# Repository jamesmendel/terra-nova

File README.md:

<h1 align="center">TERRA is a companion for mindful wandering</h1>
<h2 align="center">⭐️ This is the working repository for the second generation of TERRA hardware and software. ⭐️</h2>

<br> <!-- Additional spacing -->
<br> <!-- Additional spacing -->

<br> <!-- Additional spacing -->
<br> <!-- Additional spacing -->

##  Designed with the science of AI and the wisdom of mindfulness, TERRA is the incredible, pocket-sized compass that lets you wander without getting lost. Leave your phone behind and reconnect with your surroundings.

<br> <!-- Additional spacing -->

### Features
- **Improvised Trails, Powered by AI**: Every journey begins with a prompt. TERRA’s sophisticated AI translates your intentions, available time, and precise location into a tailored trail of GPS coordinates. Users don't know where TERRA will take them; the only certainty is finding their way back to the starting point.
- **Wander Without Your Phone**: TERRA invites users to leave their smartphones behind and reconnect with their surroundings. The standalone device boasts a minimalist interface, featuring a tranquil compass needle and gentle haptic feedback to ensure users remain engaged with the present moment.  
- **Open-Source by Design**: TERRA is designed with a DIY mindset. Anyone can download the open-source software, 3D print the CAD designs, assemble the necessary hardware, and start wandering.

<br> <!-- Additional spacing -->

<p align="center">
  ⚠️ <strong>NOTICE</strong>: This project is currently in an experimental phase and is undergoing rapid developments ⚠️
</p>

<br> <!-- Additional spacing -->

### Software

The TERRA App generates coordinates or checkpoints from a starting point and an ideal trail length using the ChatGPT API.

### Running TERRA App Locally

#### Prerequisites 
- `Node.js` v21.5
- `body-parser` v1.20.2
- `cors` v2.8.5
- `express` v4.19.0
- `node-fetch` v3.3.2

To run the TERRA App locally, follow these steps:

1. **Implement ChatGPT API Key:** Obtain a [ChatGPT API key](https://platform.openai.com/) and replace ```YOUR_OPENAI_API_KEY``` with it in the ```server.js``` file.
2. **Implement Google Maps API Key:** Obtain a [Google Places API key](https://developers.google.com/maps/documentation/places/web-service/overview) and replace ```YOUR_MAPS_KEY``` with it in the ```index.js``` file.
3. **Run Locally:** To run the application, use the command:
    ```
    node server.js
    ```
4. **Load Application:** Open `index.html` in a browser to use the app for generating a route.
5. **Download config.h File:** Download the `config.h` file which contains the generated route configuration.
6. **Update Arduino Code:** Replace the `config.h` file in the Arduino code directory with the newly downloaded file.

### Hardware

The hardware for the TERRA project is based on an ESP32 device, equipped with a range of sensors for navigation and interaction.

### Components

The main components required are:

- ESP32 Feather V2 [link](https://learn.adafruit.com/adafruit-esp32-feather-v2/pinouts)
- Waveshare 1.28" Round LCD Display Module with GC9A01 Driver [link](https://www.waveshare.com/1.28inch-lcd-module.htm)
- Adafruit Push-button Power Switch [link](https://thepihut.com/products/adafruit-push-button-power-switch-breakout)
- Beitian BN 880 GPS module [link](https://store.beitian.com/products/beitian-compass-qmc5883l-amp2-6-pix4-pixhawk-gnss-gps-glonass-dual-flight-control-gps-module-bn-880q?variant=44696120295711)
- Adafruit DRV2605L Haptic Controller Breakout [link](https://learn.adafruit.com/adafruit-drv2605-haptic-controller-breakout/arduino-code)
- CMPS12 Compass [link](https://www.robot-electronics.co.uk/cmps12-tilt-compensated-magnetic-compass.html)
- Round Battery
- USB C charging port extender

### Wiring
Connect the components together in the following order:

| ESP32 Pin | Screen | Motor Driver | Compass | GPS | Push Button |
| --------- | ------ | ------------ | ------- | --- | ----------- |
| 3V        | VCC    | VIN          | VIN     | VIN |             |
| GND       | GND    | GND          | GND     | GND | GND         |
| 19 (MOSI) | DIN    |              |         |     |             |
| 4 (A5)    | RST    |              |         |     |             |
| 5 (SCK)   | CLK    |              |         |     |             |
| 12        | BL     |              |         |     |             |
| 15        | CS     |              |         |     |             |
| 32 (A7)   |        |              |         |     | OFF         |
| 33        | DC     |              |         |     |             |
| SDA       |        | SDA          | SDA     |     |             |
| SCL       |        | SCL          | SCL     |     |             |
| RX        |        |              |         | TX  |             |
| TX        |        |              |         | RX  |             |

## Arduino Code

To run the Arduino code, you will need to set up the ESP32 board and install the necessary libraries.

### Setup Steps

1. **ESP32 Arduino Setup:** Add the ESP32 board to the Arduino IDE.
    - Go to **Arduino > Preferences**.
    - Add the following URL to the **Additional Boards Manager URLs**:
      ```
      https://raw.githubusercontent.com/espressif/arduino-esp32/gh-pages/package_esp32_dev_index.json
      ```
    - Select **Adafruit Feather ESP32 V2** as the board.

2. **Install Libraries:** Install the following libraries through the Library Manager in the Arduino IDE.
    - `TinyGPSPlus.h`
    - `TFT_eSPI.h`
    - `Adafruit_DRV2605.h`

3. **Upload the Code:** After installing the libraries and updating the `config.h` file with new coordinates, upload the code to the ESP32 device. The device should work without further adjustments.

4. **Debug Mode:** A `debugMode` flag is available in the code. To test the device with manual coordinates, set this flag to `true` and input coordinates into the serial monitor.

### Further Customizations

You can use your own checkpoint files by converting black and white images into a compatible format.

#### Using Your Own Checkpoint Files

- Convert static black and white, 240x240PX `.bmp` images to `.XBM` format using [this online tool](https://www.online-utility.org/image/convert/to/XBM).
- Open the XBM file in a text editor and copy the hexadecimal values included in the curly brackets.
- Replace the existing files in the `images/checkpoints` directory with your customized `.h` file.

### Contributors
Vision + Concept: Modem<br> 
Industrial Design: Panter&Tourron<br> 
Software + Hardware: Alice Stewart<br> 
Product Renderings: Côme Lart<br> 
Illustrations: Hugo Bernier<br> 
Campaign Teaser: Michael Willis

### License
TERRA is licensed under the GNU General Public License v3.0 © 2024 Modem

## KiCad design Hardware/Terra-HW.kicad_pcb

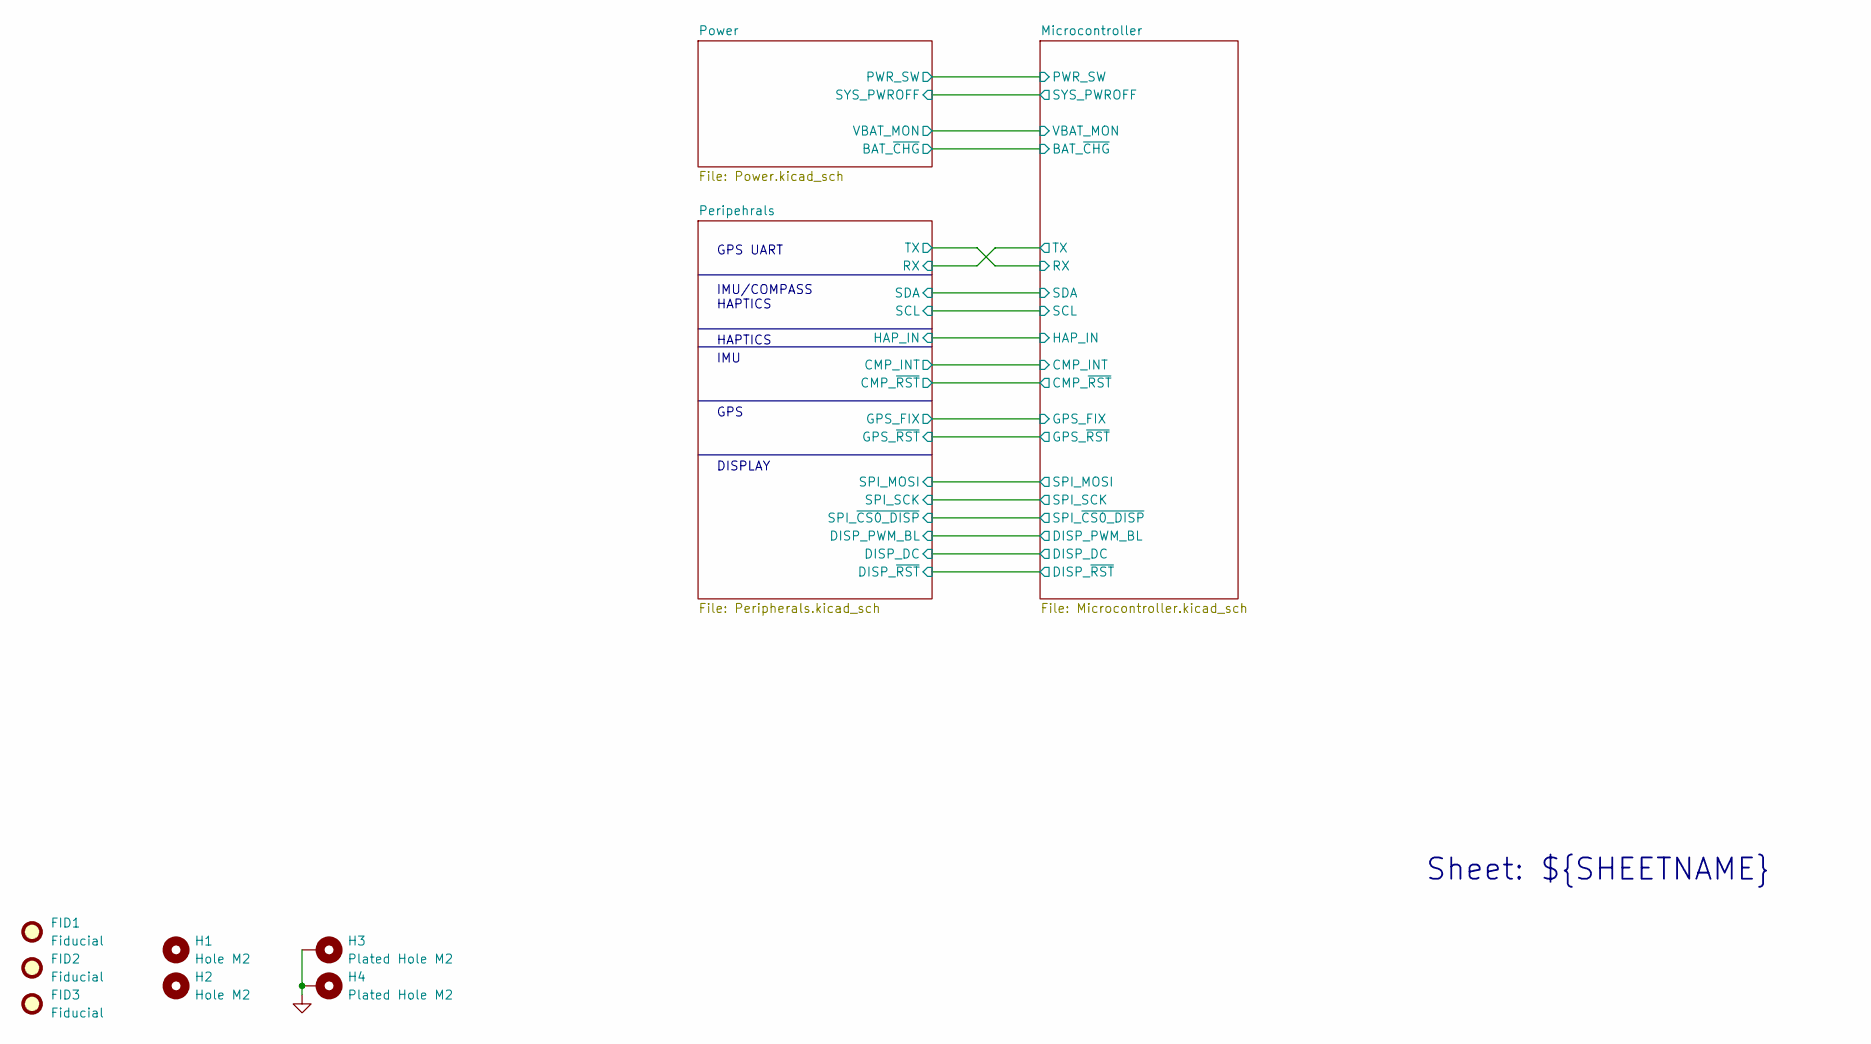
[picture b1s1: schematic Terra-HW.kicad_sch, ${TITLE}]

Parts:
FID1, FID2, FID3: Fiducial; Fiducial_1mm_Mask2mm
H1, H2: Hole M2; MountingHole_2.2mm_M2
H3, H4: Plated Hole M2; MountingHole_2.2mm_M2_Pad

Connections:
GND: H3.1, H4.1; also elsewhere on the board

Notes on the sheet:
HAPTICS
GPS UART
IMU
DISPLAY
IMU/COMPASS HAPTICS
GPS
Sheet: ${SHEETNAME}

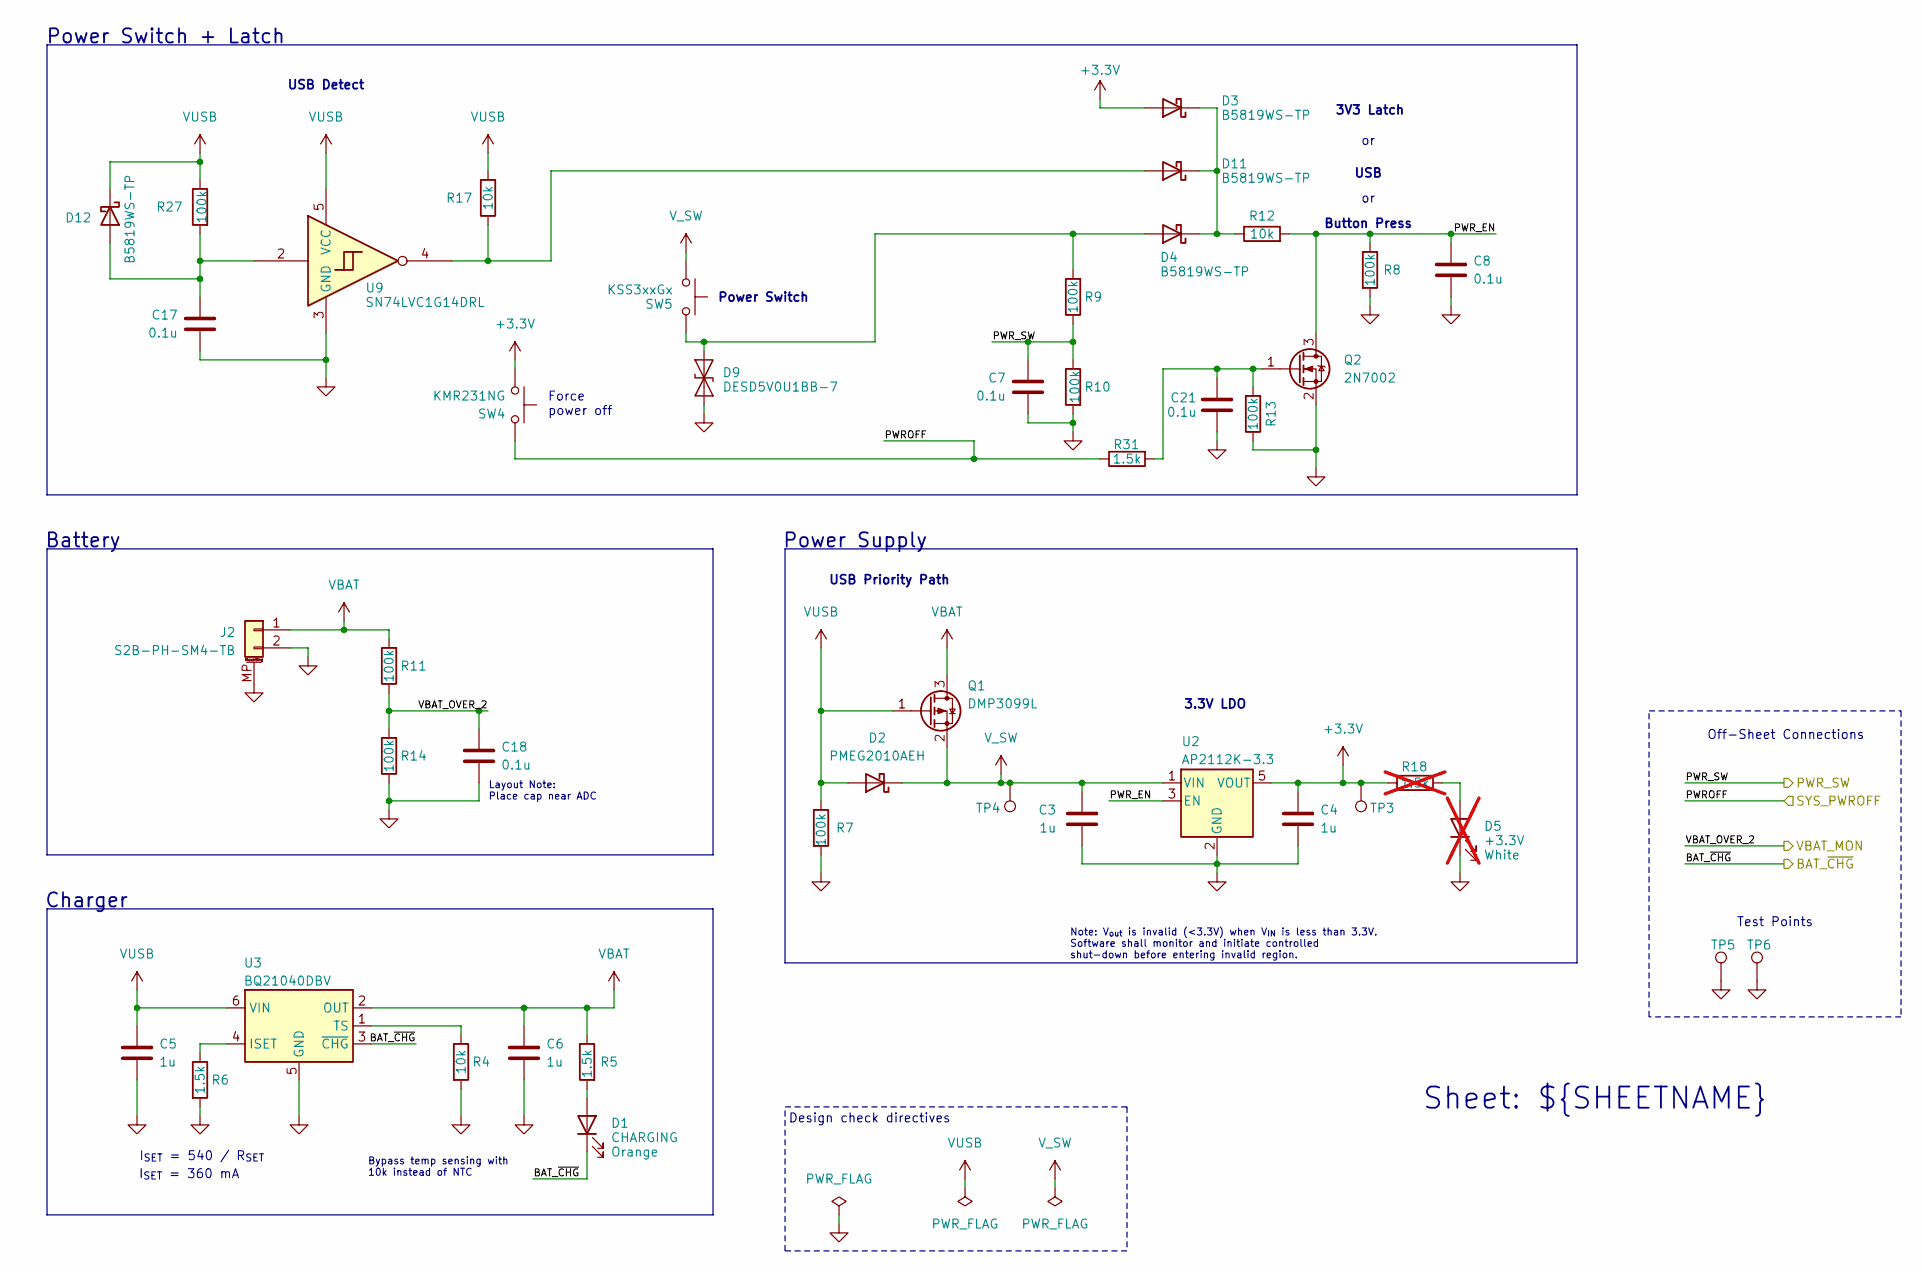
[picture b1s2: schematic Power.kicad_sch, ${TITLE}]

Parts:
C3, C4, C5, C6: 1u; C_0603_1608Metric; MPN CL10A105KO8NNNC
C7, C8, C17, C18, C21: 0.1u; C_0603_1608Metric; MPN CL10B104KO8NNNC
D1: CHARGING; D_0603_1608Metric; MPN LTST-C190KFKT
D2: PMEG2010AEH; D_SOD-123; MPN PMEG2010AEH,115
D3, D4, D11, D12: B5819WS-TP; D_SOD-323; MPN B5819WS-TP
D5: +3.3V; D_0603_1608Metric; MPN IN-S63AT5UW; not fitted
D9: DESD5V0U1BB-7; D_SOD-523; MPN DESD5V0U1BB-7
J2: S2B-PH-SM4-TB; JST_PH_S2B-PH-SM4-TB_1x02-1MP_P2.00mm_Horizontal; MPN S2B-PH-SM4-TB
Q1: DMP3099L; SOT-23; MPN DMP3099L
Q2: 2N7002; SOT-23; MPN 2N7002
R4, R12, R17: 10k; R_0603_1608Metric; MPN RC0603FR-0710KL
R5, R6, R31: 1.5k; R_0603_1608Metric; MPN RC0603FR-071K5L
R7, R8, R9, R10, R11, R13, R14, R27: 100k; R_0603_1608Metric; MPN RC0603FR-07100KL
R18: 1.5k; R_0603_1608Metric; MPN RC0603FR-071K5L; not fitted
SW4: KMR231NG; SW_Push_1P1T_NO_CK_KMR2; MPN KMR231NG
SW5: KSS3xxGx; SW_KSS323_CNK; MPN KSS321GLFS
TP3: 3.3V; TestPoint_Pad_D1.5mm_WITH_LABEL
TP4: V_SW; TestPoint_Pad_D1.5mm_WITH_LABEL
TP5, TP6: GND; TestPoint_Pad_D1.5mm_WITH_LABEL
U2: AP2112K-3.3; SOT-23-5; MPN AP2112K-3.3TRG1
U3: BQ21040DBV; SOT-23-6; MPN BQ21040DBVR
U9: SN74LVC1G14DRL; SOT-553; MPN SN74LVC1G14DRLR

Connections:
+3.3V: C4.1, D3.2 (A), R18.1, SW4.1, TP3.1, U2.5 (VOUT); also elsewhere on the board
/Microcontroller/BAT_~CHG: D1.1 (K), U3.3 (~CHG); also elsewhere on the board
/Microcontroller/PWROFF: R31.1, SW4.2; also elsewhere on the board
/Microcontroller/PWR_SW: C7.1, R9.1, R10.1; also elsewhere on the board
/Microcontroller/VBAT_OVER_2: C18.1, R11.1, R14.2; also elsewhere on the board
/Power/PWR_EN: C8.1, Q2.3 (D), R8.1, R12.2, U2.3 (EN)
GND: C3.2, C4.2, C5.2, C6.2, C7.2, C8.2, C17.2, C18.2, C21.2, D5.1 (K), D9.1 (A1), J2.2, J2.MP (MountPin), Q2.2 (S), R4.2, R6.2, R7.2, R8.2, R10.2, R13.1, R14.1, TP5.1, TP6.1, U2.2 (GND), U3.5 (GND), U9.3 (GND); also elsewhere on the board
unnamed: D1.2 (A), R5.2
unnamed: D4.2 (A), D9.2 (A2), R9.2, SW5.2
unnamed: D5.2 (A), R18.2
unnamed: D11.2 (A), R17.1, U9.4
unnamed: D3.1 (K), D4.1 (K), D11.1 (K), R12.1
unnamed: C17.1, D12.2 (A), R27.2, U9.2
unnamed: C21.1, Q2.1 (G), R13.2, R31.2
unnamed: R6.1, U3.4 (ISET)
unnamed: R4.1, U3.1 (TS)
VBAT: C6.1, J2.1, Q1.3 (D), R5.1, R11.2, U3.2 (OUT); also elsewhere on the board
VUSB: C5.1, D2.2 (A), D12.1 (K), Q1.1 (G), R7.1, R17.2, R27.1, U3.6 (VIN), U9.5 (VCC); also elsewhere on the board
V_SW: C3.1, D2.1 (K), Q1.2 (S), SW5.1, TP4.1, U2.1 (VIN)

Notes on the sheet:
Power Switch
Power Supply
I_{SET} = 540 / R_{SET}
3V3 Latch
3.3V LDO
USB Priority Path
Note: V_{out} is invalid (<3.3V) when V_{IN} is less than 3.3V. Software shall monitor and initiate controlled shut-down before entering invalid region.
Force power off
Test Points
Bypass temp sensing with 10k instead of NTC
Charger
Design check directives
I_{SET} = 360 mA
Button Press
Layout Note: Place cap near ADC
USB Detect
Battery
Off-Sheet Connections
USB
Power Switch + Latch
Sheet: ${SHEETNAME}

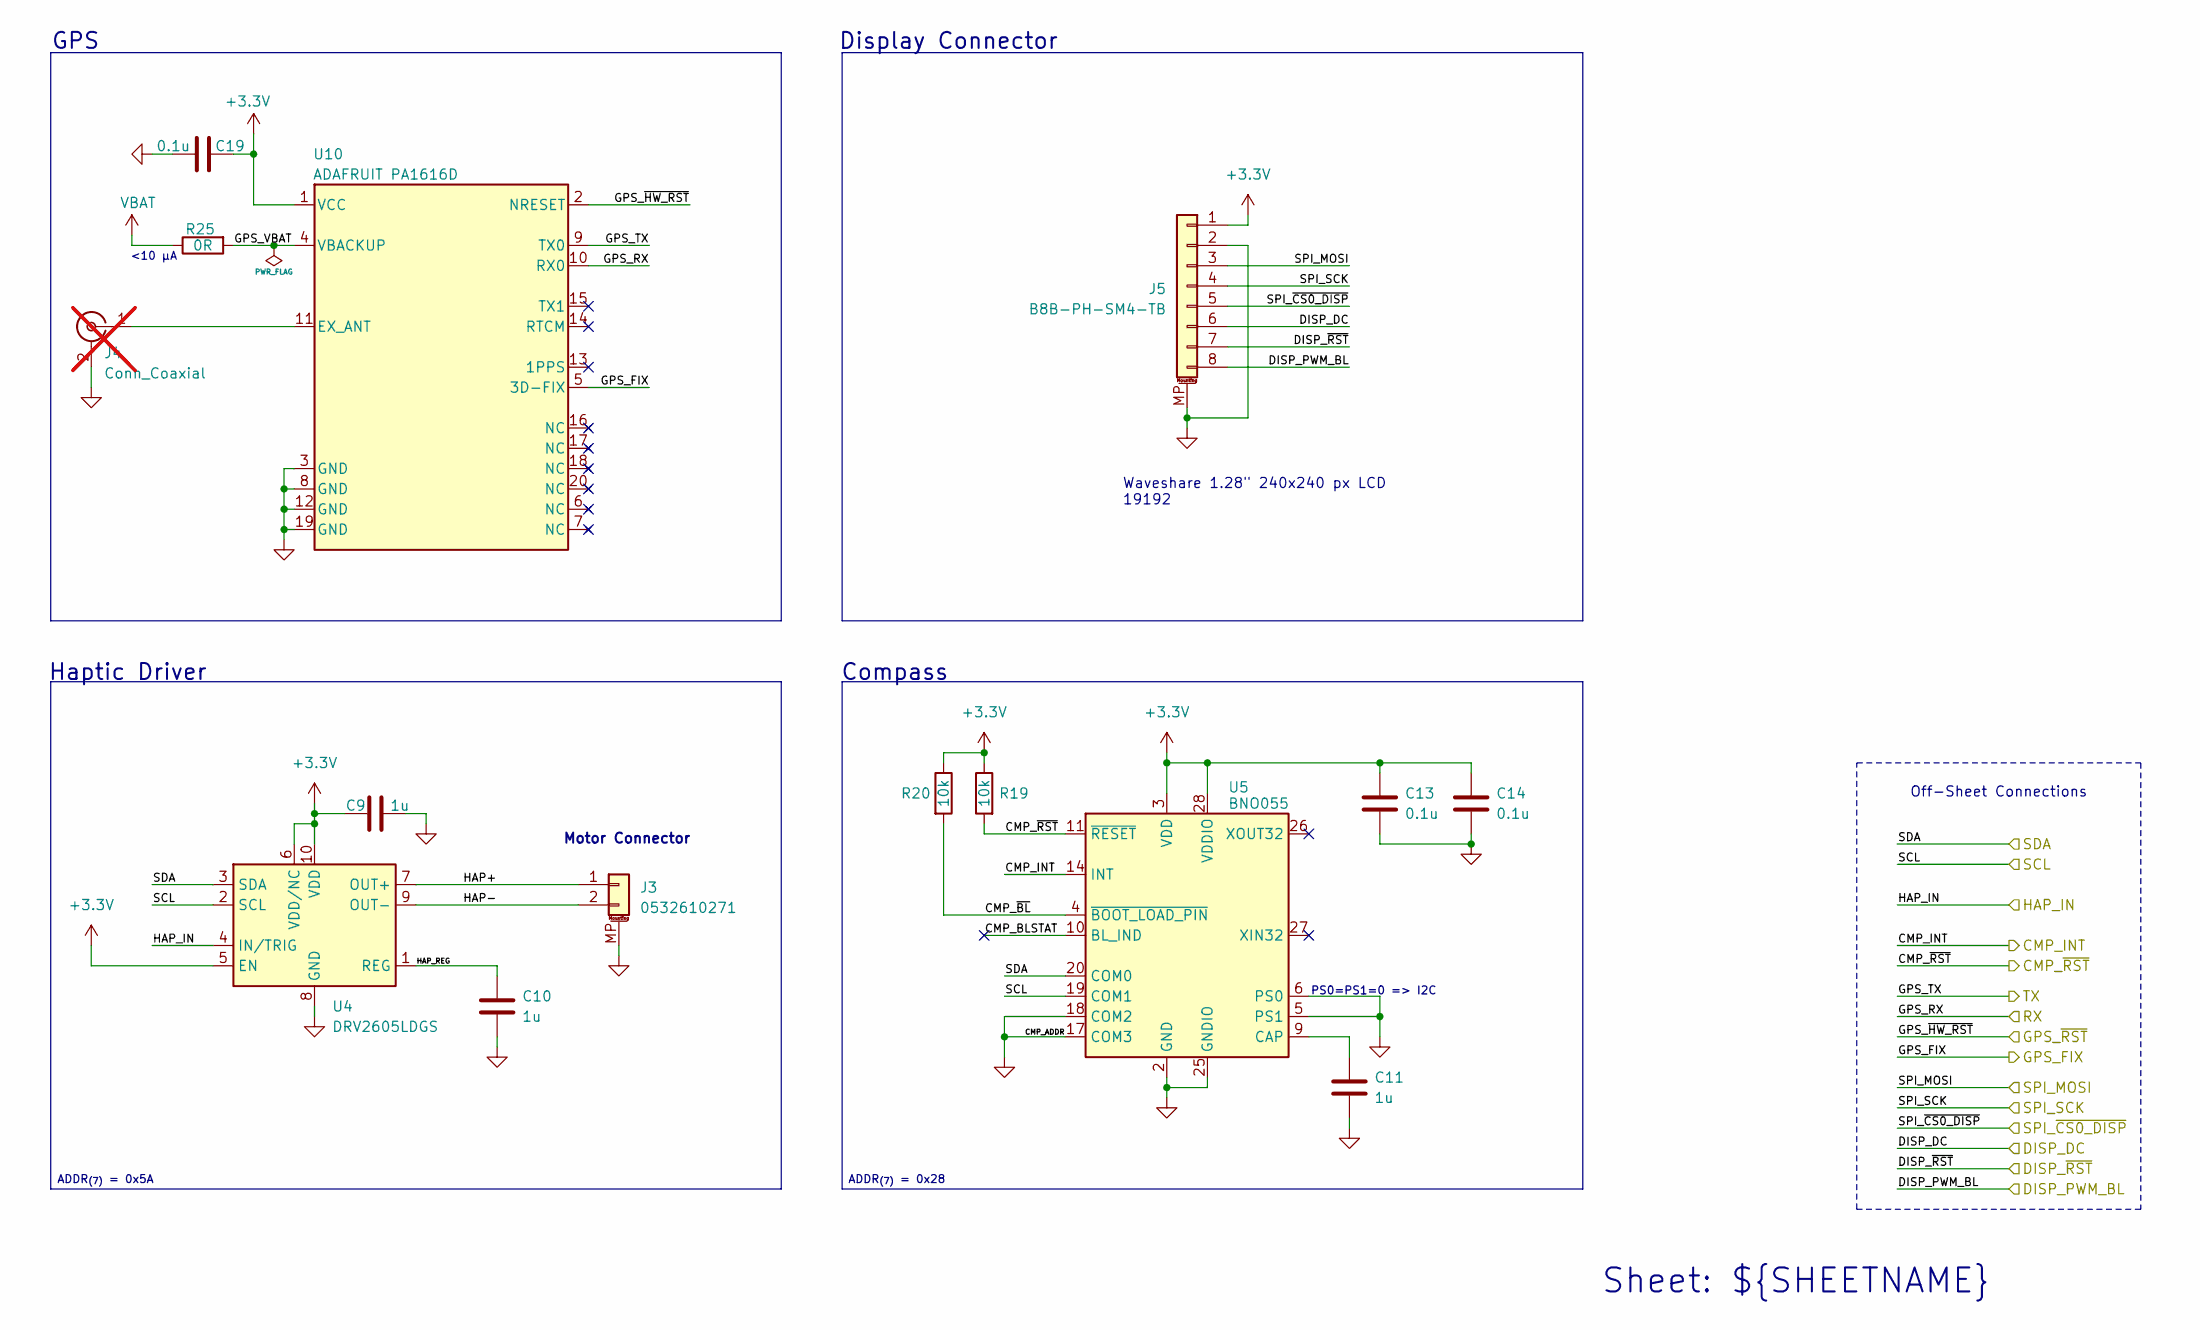
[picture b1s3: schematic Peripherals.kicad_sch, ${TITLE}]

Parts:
C9, C10, C11: 1u; C_0603_1608Metric; MPN CL10A105KO8NNNC
C13, C14, C19: 0.1u; C_0603_1608Metric; MPN CL10B104KO8NNNC
J3: 0532610271; Molex_PicoBlade_53261-0271_1x02-1MP_P1.25mm_Horizontal; MPN 0532610271
J4: Conn_Coaxial; U.FL_Molex_MCRF_73412-0110_Vertical; MPN CONMHF1-SMD-T; not fitted
J5: B8B-PH-SM4-TB; JST_PH_B8B-PH-SM4-TB_1x08-1MP_P2.00mm_Vertical; MPN B8B-PH-SM4-TB
R19, R20: 10k; R_0603_1608Metric; MPN RC0603FR-0710KL
R25: 0R; R_0603_1608Metric; MPN RC0603FR-070RL
U4: DRV2605LDGS; VSSOP-10_3x3mm_P0.5mm; MPN DRV2605LDGSR
U5: BNO055; LGA-28_5.2x3.8mm_P0.5mm; MPN BNO055
U10: ADAFRUIT PA1616D; PA1616D; MPN 5186

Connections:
+3.3V: C9.1, C13.1, C14.1, C19.1, J5.1, R19.1, R20.1, U4.5 (EN), U4.6 (VDD/NC), U4.10 (VDD), U5.3 (VDD), U5.28 (VDDIO), U10.1 (VCC); also elsewhere on the board
/Microcontroller/CMP_INT: U5.14 (INT); also elsewhere on the board
/Microcontroller/CMP_~RST: R19.2, U5.11 (~RESET); also elsewhere on the board
/Microcontroller/DISP_DC: J5.6; also elsewhere on the board
/Microcontroller/DISP_PWM_BL: J5.8; also elsewhere on the board
/Microcontroller/DISP_~RST: J5.7; also elsewhere on the board
/Microcontroller/GPS_FIX: U10.5 (3D-FIX); also elsewhere on the board
/Microcontroller/GPS_~RST: U10.2 (NRESET); also elsewhere on the board
/Microcontroller/HAPTIC_IN_TRG: U4.4 (IN/TRIG); also elsewhere on the board
/Microcontroller/I2C_SCL: U4.2 (SCL), U5.19 (COM1); also elsewhere on the board
/Microcontroller/I2C_SDA: U4.3 (SDA), U5.20 (COM0); also elsewhere on the board
/Microcontroller/SPI_MOSI: J5.3; also elsewhere on the board
/Microcontroller/SPI_SCK: J5.4; also elsewhere on the board
/Microcontroller/SPI_~CS0_DISP: J5.5; also elsewhere on the board
/Microcontroller/U1RXD: U10.9 (TX0); also elsewhere on the board
/Microcontroller/U1TXD: U10.10 (RX0); also elsewhere on the board
/Peripehrals/CMP_BLSTAT: U5.10 (BL_IND)
/Peripehrals/CMP_~BL: R20.2, U5.4 (~BOOT_LOAD_PIN)
/Peripehrals/GPS_VBAT: R25.2, U10.4 (VBACKUP)
/Peripehrals/HAP+: J3.1, U4.7 (OUT+)
/Peripehrals/HAP-: J3.2, U4.9 (OUT-)
/Peripehrals/HAP_REG: C10.1, U4.1 (REG)
GND: C9.2, C10.2, C11.2, C13.2, C14.2, C19.2, J3.MP (MountPin), J4.2 (Ext), J5.2, J5.MP (MountPin), U4.8 (GND), U5.2 (GND), U5.5 (PS1), U5.6 (PS0), U5.17 (COM3), U5.18 (COM2), U5.25 (GNDIO), U10.3 (GND), U10.8 (GND), U10.12 (GND), U10.19 (GND); also elsewhere on the board
unnamed: J4.1 (In), U10.11 (EX_ANT)
unnamed: C11.1, U5.9 (CAP)
VBAT: R25.1; also elsewhere on the board

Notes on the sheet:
ADDR_{(7)} = 0x5A
ADDR_{(7)} = 0x28
Off-Sheet Connections
Waveshare 1.28" 240x240 px LCD 19192
Motor Connector
Compass
GPS
<10 μA
PS0=PS1=0 => I2C
Haptic Driver
Display Connector
Sheet: ${SHEETNAME}

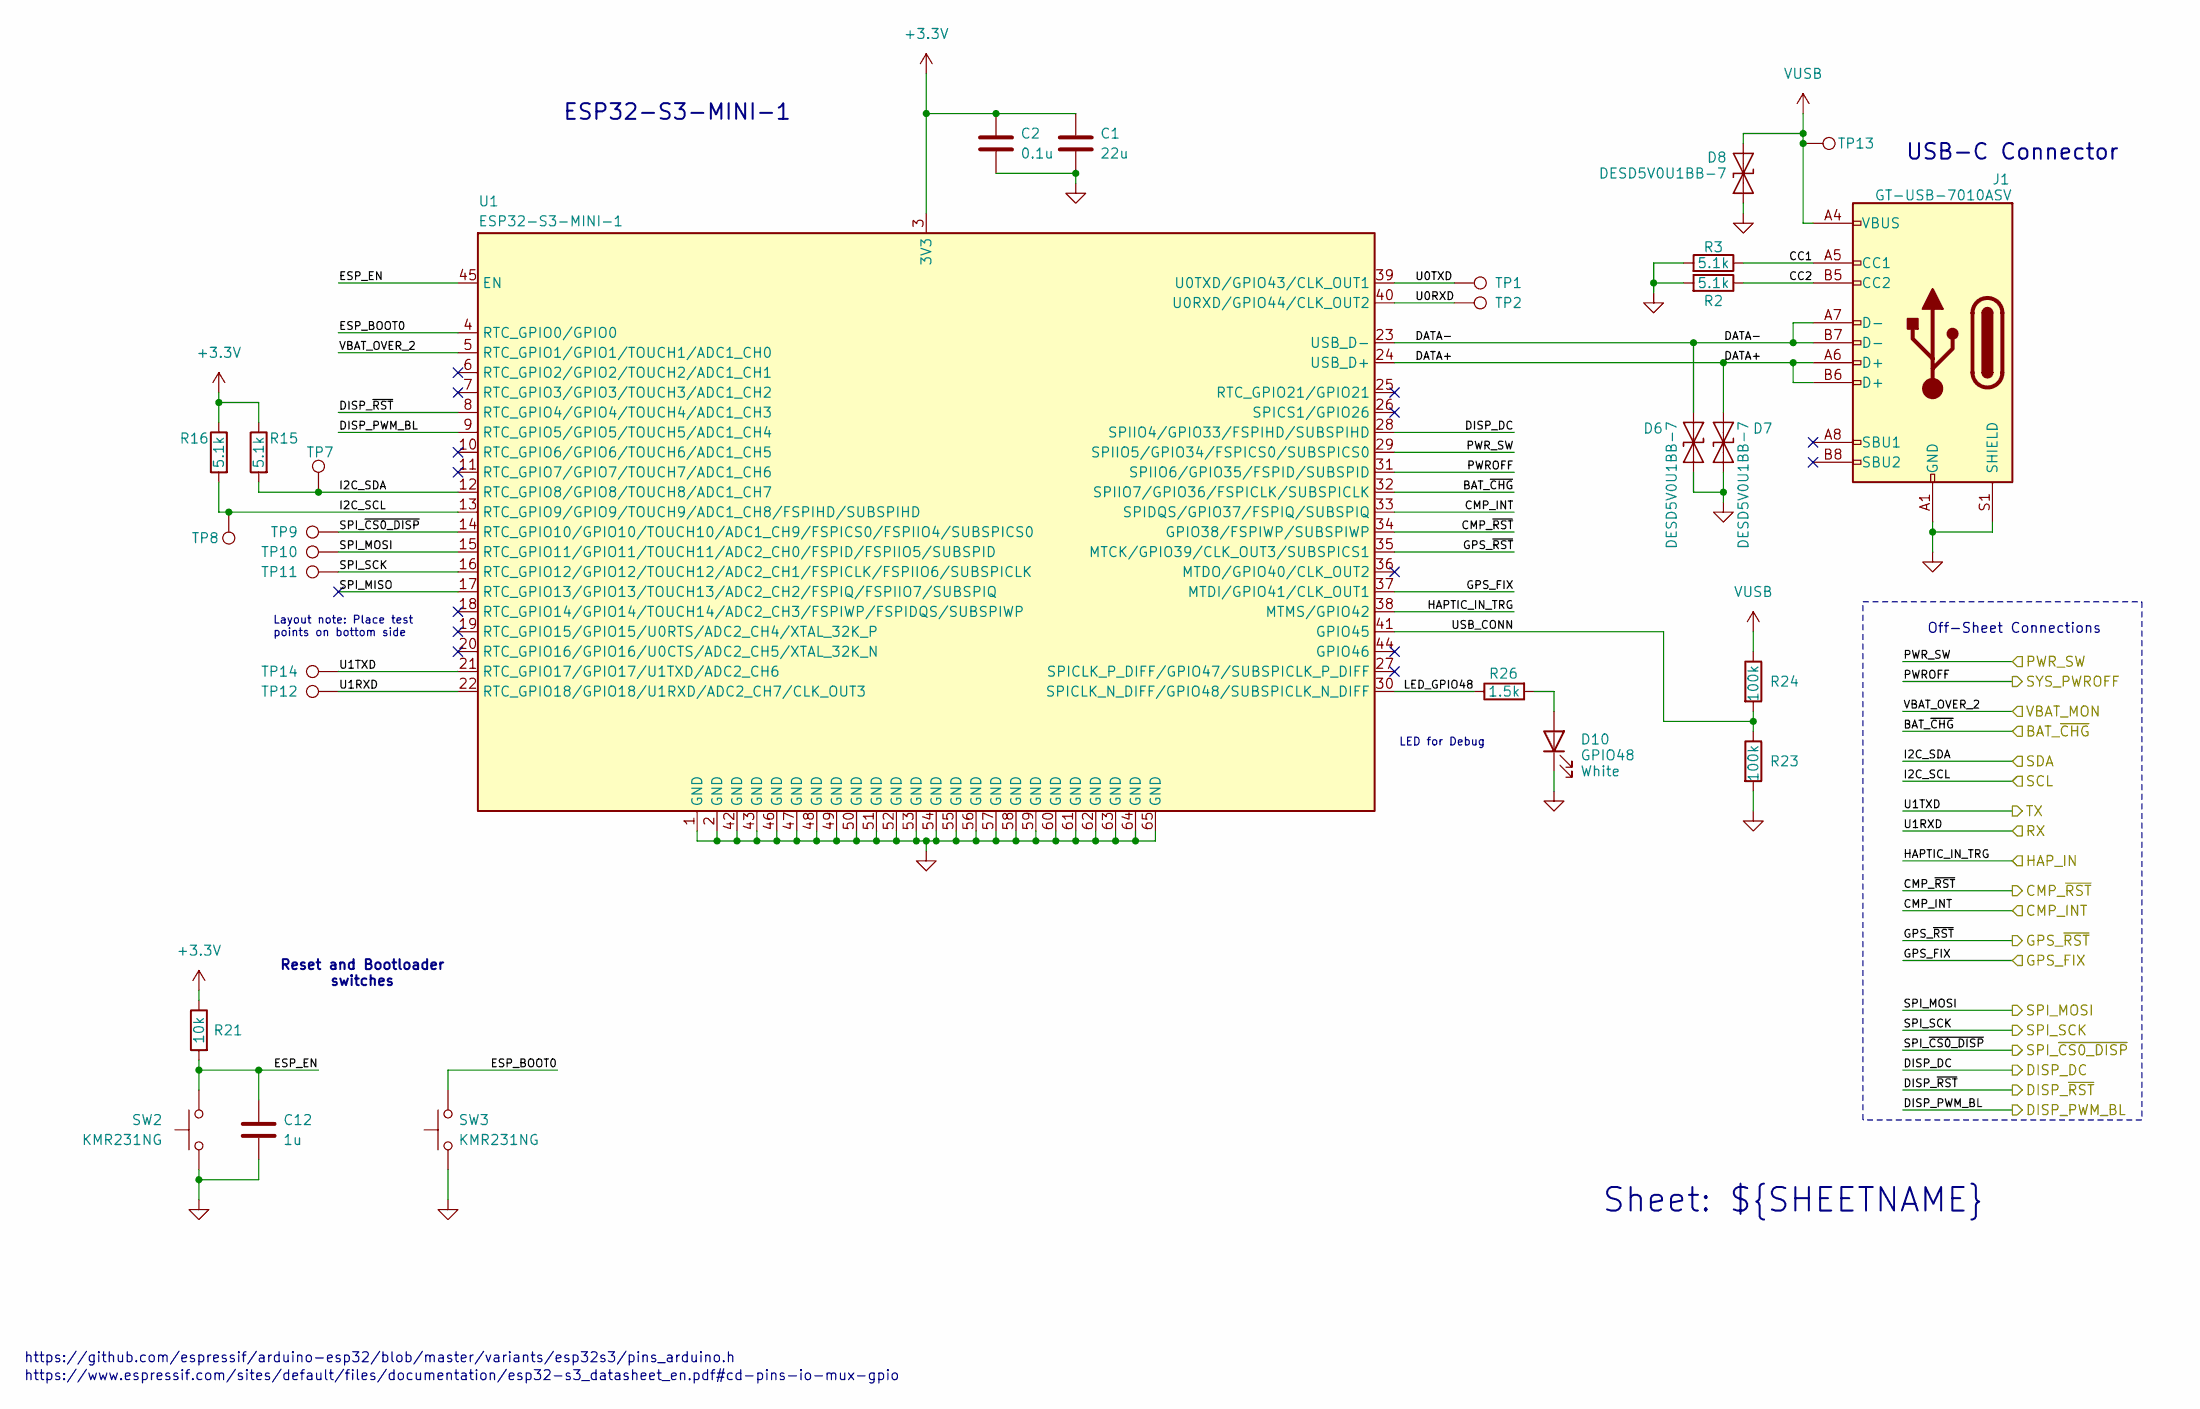
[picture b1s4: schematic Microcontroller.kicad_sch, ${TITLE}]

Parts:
C1: 22u; C_0603_1608Metric; MPN CL10A226MP8NUNE
C2: 0.1u; C_0603_1608Metric; MPN CL10B104KO8NNNC
C12: 1u; C_0603_1608Metric; MPN CL10A105KO8NNNC
D6, D7, D8: DESD5V0U1BB-7; D_SOD-523; MPN DESD5V0U1BB-7
D10: GPIO48; D_0603_1608Metric; MPN IN-S63AT5UW
J1: GT-USB-7010ASV; USB_C_Receptacle_G-Switch_GT-USB-7010ASV; MPN GT-USB-7010ASV
R2, R3, R15, R16: 5.1k; R_0603_1608Metric; MPN RC0603FR-075K1L
R21: 10k; R_0603_1608Metric; MPN RC0603FR-0710KL
R23, R24: 100k; R_0603_1608Metric; MPN RC0603FR-07100KL
R26: 1.5k; R_0603_1608Metric; MPN RC0603FR-071K5L
SW2, SW3: KMR231NG; SW_Push_1P1T_NO_CK_KMR2; MPN KMR231NG
TP1: TXD0; TestPoint_Pad_D1.5mm_WITH_LABEL
TP2: RXD0; TestPoint_Pad_D1.5mm_WITH_LABEL
TP7: I2C_SDA; TestPoint_Pad_D1.5mm_WITH_LABEL
TP8: I2C_SCL; TestPoint_Pad_D1.5mm_WITH_LABEL
TP9: SPI_CS0; TestPoint_Pad_D1.5mm_WITH_LABEL
TP10: SPI_MOSI; TestPoint_Pad_D1.5mm_WITH_LABEL
TP11: SPI_SCK; TestPoint_Pad_D1.5mm_WITH_LABEL
TP12: RXD1; TestPoint_Pad_D1.5mm_WITH_LABEL
TP13: VUSB; TestPoint_Pad_D1.5mm_WITH_LABEL
TP14: TXD1; TestPoint_Pad_D1.5mm_WITH_LABEL
U1: ESP32-S3-MINI-1; ESP32-S2-MINI-1; MPN ESP32-S3-MINI-1-N4R2

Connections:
+3.3V: C1.1, C2.1, R15.1, R16.1, R21.1, U1.3 (3V3); also elsewhere on the board
/Microcontroller/BAT_~CHG: U1.32 (SPIIO7/GPIO36/FSPICLK/SUBSPICLK); also elsewhere on the board
/Microcontroller/CC1: J1.A5 (CC1), R3.1
/Microcontroller/CC2: J1.B5 (CC2), R2.1
/Microcontroller/CMP_INT: U1.33 (SPIDQS/GPIO37/FSPIQ/SUBSPIQ); also elsewhere on the board
/Microcontroller/CMP_~RST: U1.34 (GPIO38/FSPIWP/SUBSPIWP); also elsewhere on the board
/Microcontroller/DATA+: D7.2 (A2), J1.A6 (D+), J1.B6 (D+), U1.24 (USB_D+)
/Microcontroller/DATA-: D6.2 (A2), J1.A7 (D-), J1.B7 (D-), U1.23 (USB_D-)
/Microcontroller/DISP_DC: U1.28 (SPIIO4/GPIO33/FSPIHD/SUBSPIHD); also elsewhere on the board
/Microcontroller/DISP_PWM_BL: U1.9 (RTC_GPIO5/GPIO5/TOUCH5/ADC1_CH4); also elsewhere on the board
/Microcontroller/DISP_~RST: U1.8 (RTC_GPIO4/GPIO4/TOUCH4/ADC1_CH3); also elsewhere on the board
/Microcontroller/ESP_BOOT0: SW3.2, U1.4 (RTC_GPIO0/GPIO0)
/Microcontroller/ESP_EN: C12.1, R21.2, SW2.2, U1.45 (EN)
/Microcontroller/GPS_FIX: U1.37 (MTDI/GPIO41/CLK_OUT1); also elsewhere on the board
/Microcontroller/GPS_~RST: U1.35 (MTCK/GPIO39/CLK_OUT3/SUBSPICS1); also elsewhere on the board
/Microcontroller/HAPTIC_IN_TRG: U1.38 (MTMS/GPIO42); also elsewhere on the board
/Microcontroller/I2C_SCL: R16.2, TP8.1, U1.13 (RTC_GPIO9/GPIO9/TOUCH9/ADC1_CH8/FSPIHD/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); also elsewhere on the board
/Microcontroller/I2C_SDA: R15.2, TP7.1, U1.12 (RTC_GPIO8/GPIO8/TOUCH8/ADC1_CH7); also elsewhere on the board
/Microcontroller/LED_GPIO48: R26.1, U1.30 (SPICLK_N_DIFF/GPIO48/SUBSPICLK_N_DIFF)
/Microcontroller/PWROFF: U1.31 (SPIIO6/GPIO35/FSPID/SUBSPID); also elsewhere on the board
/Microcontroller/PWR_SW: U1.29 (SPIIO5/GPIO34/FSPICS0/SUBSPICS0); also elsewhere on the board
/Microcontroller/SPI_MISO: U1.17 (RTC_GPIO13/GPIO13/TOUCH13/ADC2_CH2/FSPI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)
/Microcontroller/SPI_MOSI: TP10.1, U1.15 (RTC_GPIO11/GPIO11/TOUCH11/ADC2_CH0/FSPI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); also elsewhere on the board
/Microcontroller/SPI_SCK: TP11.1, U1.16 (RTC_GPIO12/GPIO12/TOUCH12/ADC2_CH1/FSPI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); also elsewhere on the board
/Microcontroller/SPI_~CS0_DISP: TP9.1, U1.14 (RTC_GPIO10/GPIO10/TOUCH10/ADC1_CH9/FSPI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); also elsewhere on the board
/Microcontroller/U0RXD: TP2.1, U1.40 (U0RXD/GPIO44/CLK_OUT2)
/Microcontroller/U0TXD: TP1.1, U1.39 (U0TXD/GPIO43/CLK_OUT1)
/Microcontroller/U1RXD: TP12.1, U1.22 (RTC_GPIO18/GPIO18/U1RXD/ADC2_CH7/CLK_OU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); also elsewhere on the board
/Microcontroller/U1TXD: TP14.1, U1.21 (RTC_GPIO17/GPIO17/U1TXD/ADC2_CH6); also elsewhere on the board
/Microcontroller/USB_CONN: R23.1, R24.2, U1.41 (GPIO45)
/Microcontroller/VBAT_OVER_2: U1.5 (RTC_GPIO1/GPIO1/TOUCH1/ADC1_CH0); also elsewhere on the board
GND: C1.2, C2.2, C12.2, D6.1 (A1), D7.1 (A1), D8.1 (A1), D10.1 (K), J1.A1 (GND), J1.A12 (GND), J1.B1 (GND), J1.B12 (GND), J1.S1 (SHIELD), R2.2, R3.2, R23.2, SW2.1, SW3.1, U1.1 (GND), U1.2 (GND), U1.42 (GND), U1.43 (GND), U1.46 (GND), U1.47 (GND), U1.48 (GND), U1.49 (GND), U1.50 (GND), U1.51 (GND), U1.52 (GND), U1.53 (GND), U1.54 (GND), U1.55 (GND), U1.56 (GND), U1.57 (GND), U1.58 (GND), U1.59 (GND), U1.60 (GND), U1.61 (GND), U1.62 (GND), U1.63 (GND), U1.64 (GND), U1.65 (GND); also elsewhere on the board
unnamed: D10.2 (A), R26.2
VUSB: D8.2 (A2), J1.A4 (VBUS), J1.A9 (VBUS), J1.B4 (VBUS), J1.B9 (VBUS), R24.1, TP13.1; also elsewhere on the board

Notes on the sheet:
https://github.com/espressif/arduino-esp32/blob/master/variants/esp32s3/pins_arduino.h
Reset and Bootloader switches
https://www.espressif.com/sites/default/files/documentation/esp32-s3_datasheet_en.pdf#cd-pins-io-mux-gpio
Layout note: Place test points on bottom side
USB-C Connector
ESP32-S3-MINI-1
Off-Sheet Connections
LED for Debug
Sheet: ${SHEETNAME}

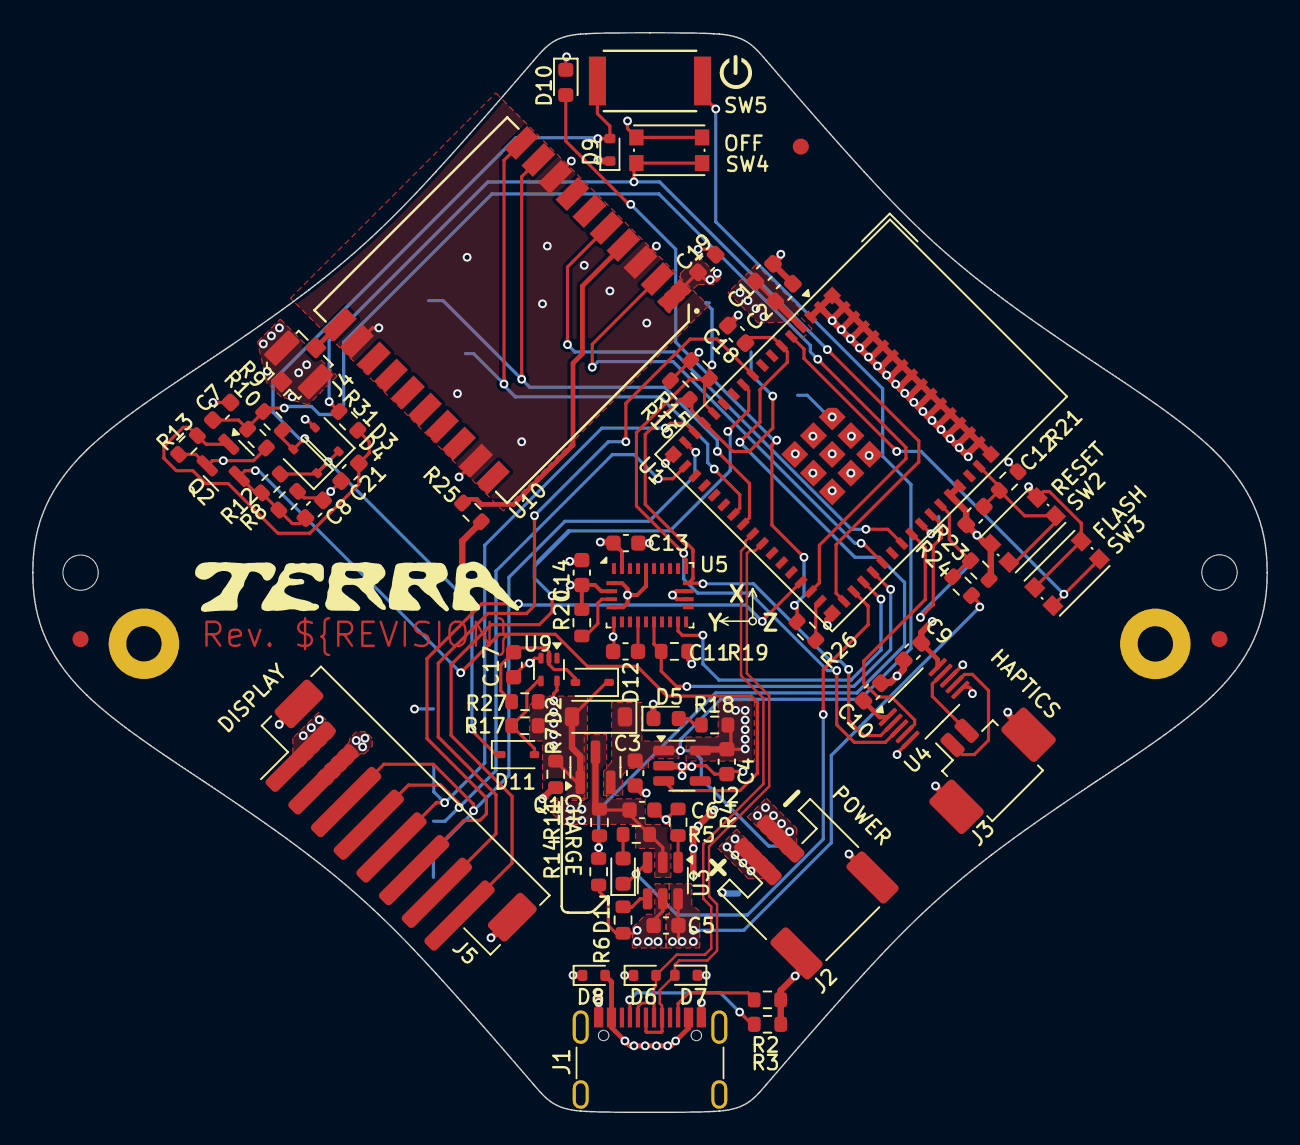
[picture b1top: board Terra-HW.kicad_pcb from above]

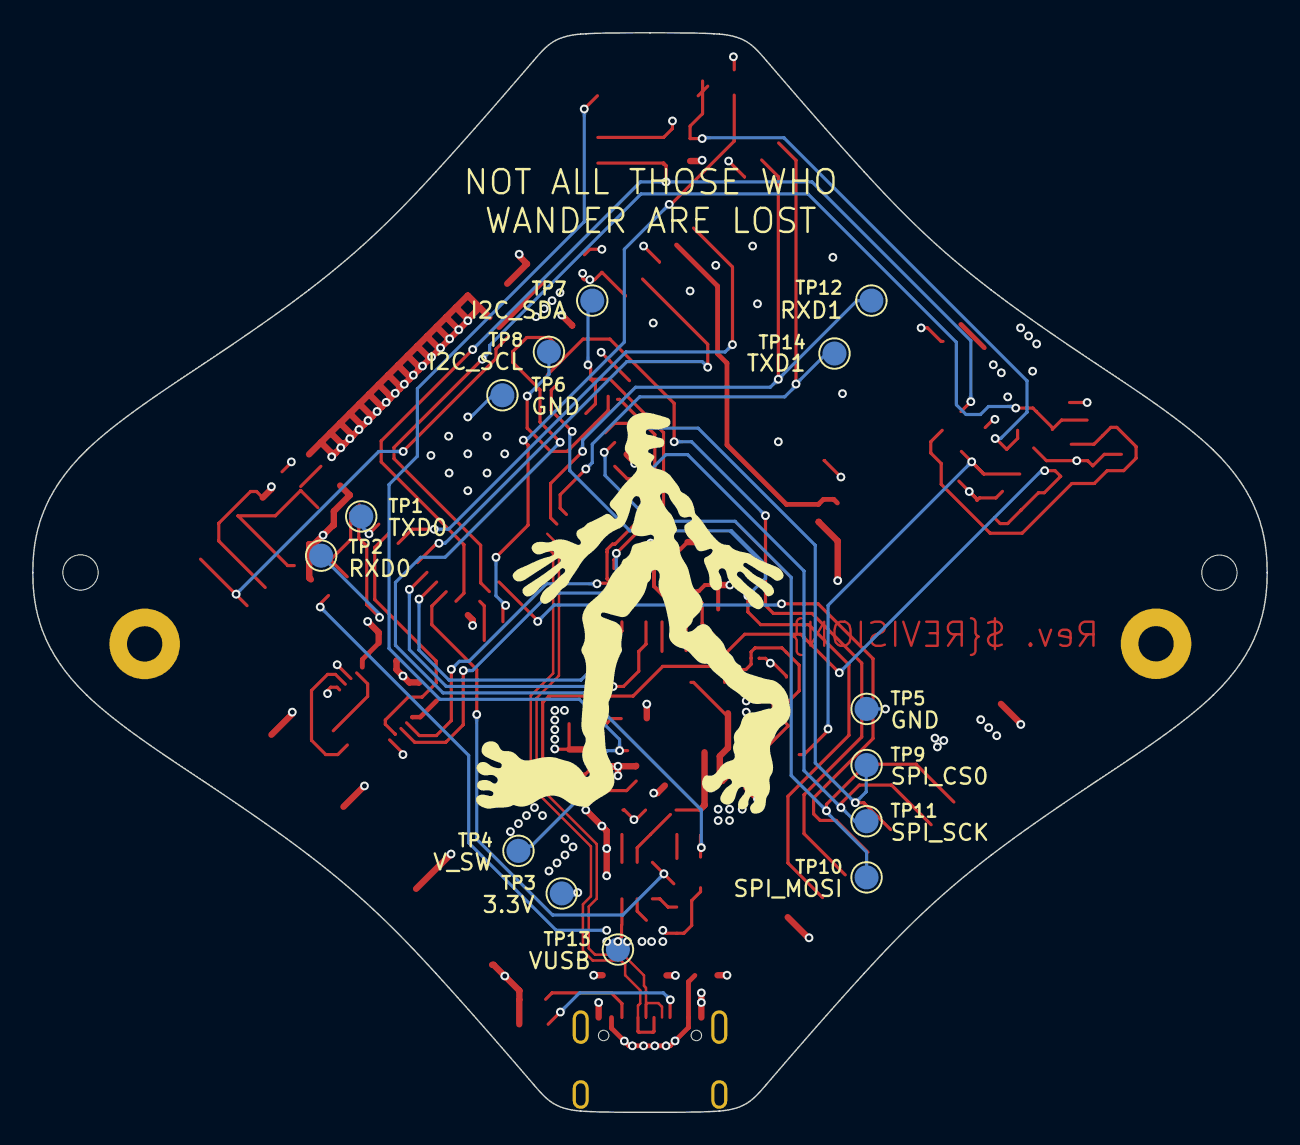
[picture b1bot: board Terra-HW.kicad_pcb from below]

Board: 4 copper layers, 76.9 x 67.3 mm, 95 parts (14 on the bottom side), 52 nets.

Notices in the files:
parts and their libraries:
COPYRIGHT: Copyright 2025
LICENSE: Licensed under GNU GPL v3.0
